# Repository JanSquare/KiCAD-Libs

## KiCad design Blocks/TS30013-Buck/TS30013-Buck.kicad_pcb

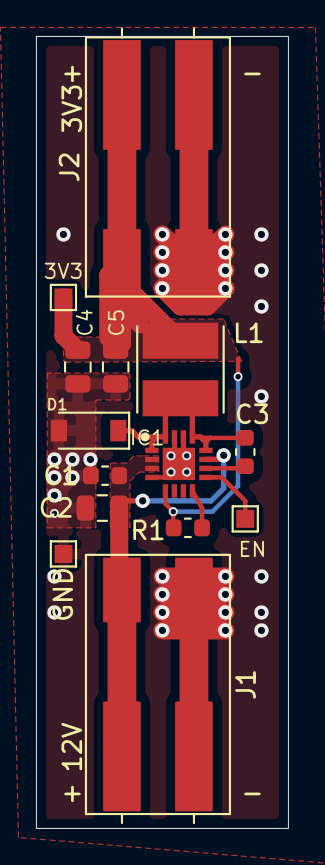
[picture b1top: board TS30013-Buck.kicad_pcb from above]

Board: 2 copper layers, 14.0 x 44.0 mm, 14 parts (0 on the bottom side), 8 nets.

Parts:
3V3: TestPoint; TestPoint_Pad_1.0x1.0mm
C1, C3: 100nF 50V; C_0603_1608Metric
C2: 10uF 35V; C_0805_2012Metric
C4, C5: 22uF 10V; C_0805_2012Metric
D1: D_Schottky; D_SOD-123
EN: TestPoint; TestPoint_Pad_1.0x1.0mm
GND: TestPoint; TestPoint_Pad_1.0x1.0mm
IC1: TS30013-M033QFNR; QFN50P300X300X100-17N-D
J1, J2: Screw_Terminal_01x02; WAGO_2060-452-998-404
L1: 4.7uH; L_BOURNS_4828A
R1: 10k; R_0603_1608Metric

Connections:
+3V3: 3V3.1, C4.1, C5.1, IC1.5, J2.2, L1.1, R1.1
+12V: C1.1, C2.1, IC1.2, IC1.3, IC1.11, J1.1
GND: C1.2, C2.2, C4.2, C5.2, D1.2, GND.1, J1.2, J2.1
unnamed: C3.1, D1.1, IC1.1, IC1.12, IC1.13, IC1.16, L1.2
unnamed: C3.2, IC1.10
unnamed: IC1.8, R1.2
unnamed: EN.1, IC1.9
unnamed: IC1.4, IC1.14, IC1.15, IC1.17

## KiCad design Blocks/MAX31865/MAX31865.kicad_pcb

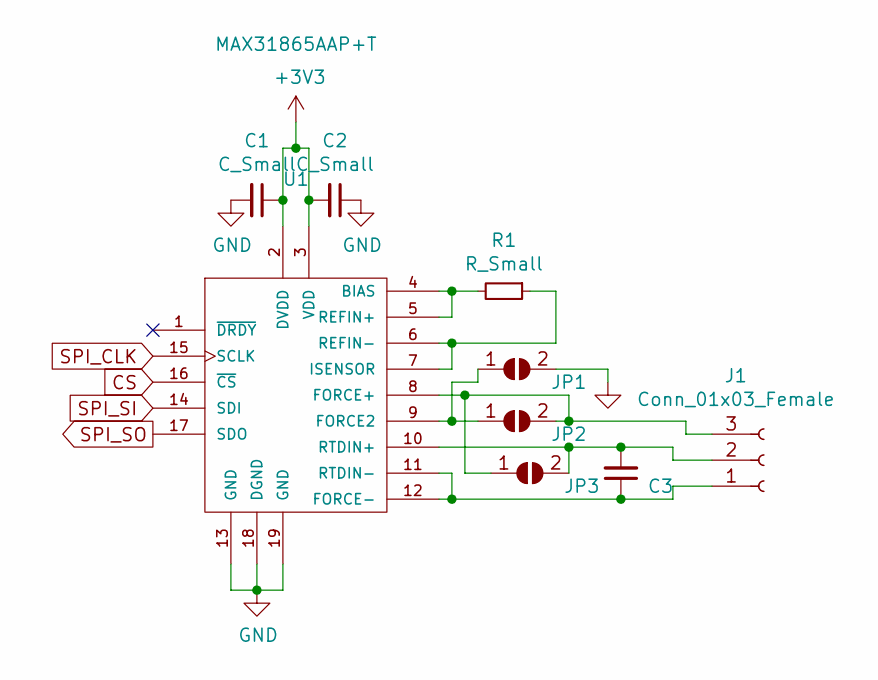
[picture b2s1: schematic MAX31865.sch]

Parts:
C1, C2, C3: C_Small; C_0603_1608Metric
J1: Conn_01x03_Female; WAGO_2059-303_998-403
JP1, JP2, JP3: SolderJumper_2_Open; SolderJumper-2_P1.3mm_Open_TrianglePad1.0x1.5mm
R1: R_Small; R_0603_1608Metric
U1: MAX31865AAP+T; SOP65P777X199-20N

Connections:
+3V3: C1.1, C2.2, U1.2 (DVDD), U1.3 (VDD)
CS: U1.16 (~CS~)
GND: C1.2, C2.1, JP1.2 (B), U1.13 (GND), U1.18 (DGND), U1.19 (GND)
unnamed: C3.1, J1.1, U1.11 (RTDIN-), U1.12 (FORCE-)
unnamed: C3.2, J1.2, JP3.2 (B), U1.10 (RTDIN+)
unnamed: J1.3, JP2.2 (B), JP3.1 (A), U1.8 (FORCE+)
unnamed: JP1.1 (A), JP2.1 (A), U1.9 (FORCE2)
unnamed: R1.1, U1.6 (REFIN-), U1.7 (ISENSOR)
unnamed: R1.2, U1.4 (BIAS), U1.5 (REFIN+)
SPI_CLK: U1.15 (SCLK)
SPI_SI: U1.14 (SDI)
SPI_SO: U1.17 (SDO)

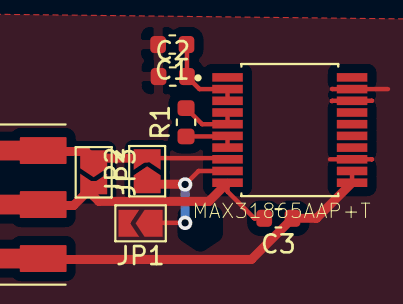
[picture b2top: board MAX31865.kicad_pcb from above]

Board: 2 copper layers, 9 parts (0 on the bottom side), 8 nets.

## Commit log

2019-12-14 init
2019-12-15 added Blocks
2019-12-21 updated WS142R-5.08-3P
2020-02-24 added parts and footprints
2020-02-24 pj002bh
